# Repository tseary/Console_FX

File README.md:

# Console_FX
Controller for steam power plant control console "light show".

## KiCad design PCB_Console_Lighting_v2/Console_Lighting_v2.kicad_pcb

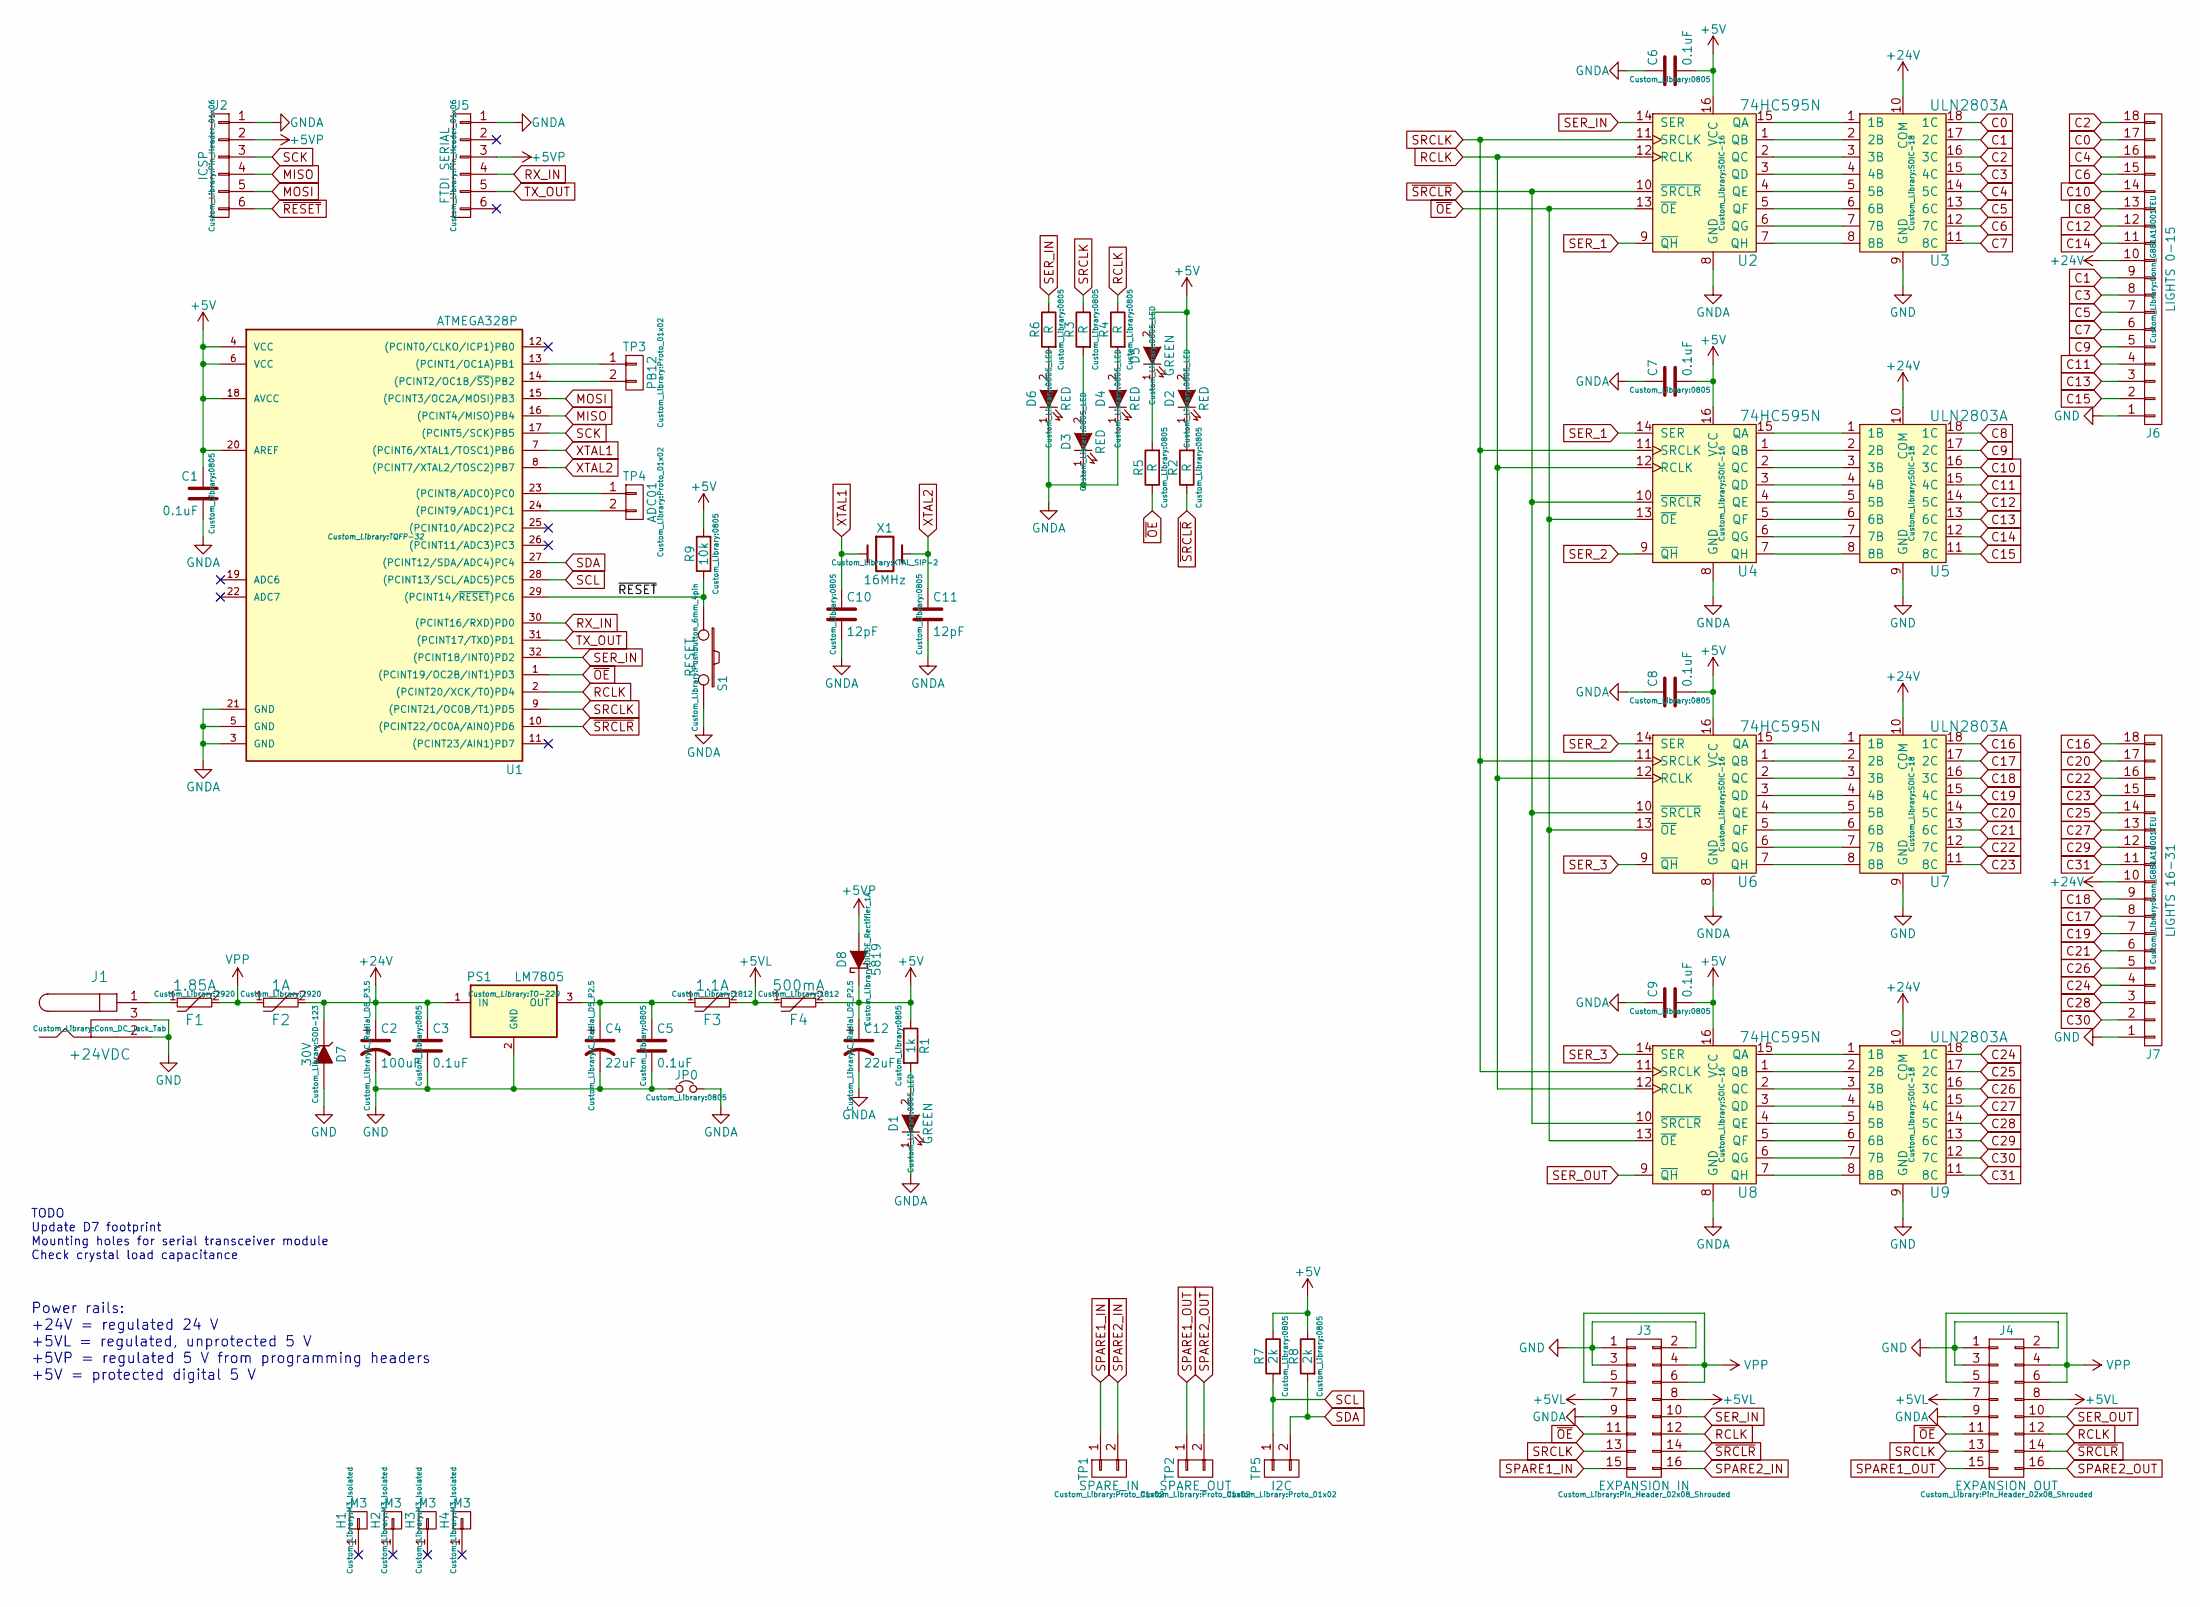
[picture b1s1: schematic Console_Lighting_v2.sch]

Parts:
C1, C3, C5, C6, C7, C8, C9: 0.1uF; 0805
C2: 100uF; C_Radial_D8_P3.5
C4, C12: 22uF; C_Radial_D5_P2.5
C10, C11: 12pF; 0805
D1, D5: GREEN; 0805_LED
D2, D3, D4, D6: RED; 0805_LED
D7: 30V; SOD-123
D8: 5819; DIODE_Rectifier_1A
F1: 1.85A; 2920
F2: 1A; 2920
F3: 1.1A; 1812
F4: 500mA; 1812
H1, H2, H3, H4: M3; M3_Isolated
J1: +24VDC; Conn_DC_Jack_Tab
J2: ICSP; Pin_Header_01x06
J3: EXPANSION IN; Pin_Header_02x08_Shrouded
J4: EXPANSION OUT; Pin_Header_02x08_Shrouded
J5: FTDI SERIAL; Pin_Header_01x06
J6: LIGHTS 0-15; Conn_G881A18001TEU
J7: LIGHTS 16-31; Conn_G881A18001TEU
JP0: Jumper_NC_Small; 0805
PS1: LM7805; TO-220
R1: 1k; 0805
R2, R3, R4, R5, R6: R; 0805
R7, R8: 2k; 0805
R9: 10k; 0805
S1: RESET; Pushbutton_6mm_4pin
TP1: SPARE_IN; Proto_01x02
TP2: SPARE_OUT; Proto_01x02
TP3: PB12; Proto_01x02
TP4: ADC01; Proto_01x02
TP5: I2C; Proto_01x02
U1: ATMEGA328P; TQFP-32
U2, U4, U6, U8: 74HC595N; SOIC-16
U3, U5, U7, U9: ULN2803A; SOIC-18
X1: 16MHz; XTAL_SIP-2

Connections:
+5V: C1.1, C6.2, C7.2, C8.2, C9.2, C12.1, D2.2 (A), D5.2 (A), D8.1 (K), F4.2, R1.1, R7.1, R8.1, R9.2, U1.4 (VCC), U1.6 (VCC), U1.18 (AVCC), U1.20 (AREF), U2.16 (VCC), U4.16 (VCC), U6.16 (VCC), U8.16 (VCC)
+5VL: F3.2, F4.1, J3.7, J3.8, J4.7, J4.8
+5VP: D8.2 (A), J2.2, J5.3
+24V: C2.1, C3.1, D7.1 (K), F2.2, J6.10, J7.10, PS1.1 (IN), U3.10 (COM), U5.10 (COM), U7.10 (COM), U9.10 (COM)
C0: J6.17, U3.18 (1C)
C1: J6.9, U3.17 (2C)
C2: J6.18, U3.16 (3C)
C3: J6.8, U3.15 (4C)
C4: J6.16, U3.14 (5C)
C5: J6.7, U3.13 (6C)
C6: J6.15, U3.12 (7C)
C7: J6.6, U3.11 (8C)
C8: J6.13, U5.18 (1C)
C9: J6.5, U5.17 (2C)
C10: J6.14, U5.16 (3C)
C11: J6.4, U5.15 (4C)
C12: J6.12, U5.14 (5C)
C13: J6.3, U5.13 (6C)
C14: J6.11, U5.12 (7C)
C15: J6.2, U5.11 (8C)
C16: J7.18, U7.18 (1C)
C17: J7.8, U7.17 (2C)
C18: J7.9, U7.16 (3C)
C19: J7.7, U7.15 (4C)
C20: J7.17, U7.14 (5C)
C21: J7.6, U7.13 (6C)
C22: J7.16, U7.12 (7C)
C23: J7.15, U7.11 (8C)
C24: J7.4, U9.18 (1C)
C25: J7.14, U9.17 (2C)
C26: J7.5, U9.16 (3C)
C27: J7.13, U9.15 (4C)
C28: J7.3, U9.14 (5C)
C29: J7.12, U9.13 (6C)
C30: J7.2, U9.12 (7C)
C31: J7.11, U9.11 (8C)
GND: C2.2, C3.2, C4.2, C5.2, D7.2 (A), J1.2, J1.3, J3.1, J3.2, J3.3, J4.1, J4.2, J4.3, J6.1, J7.1, JP0.1, PS1.2 (GND), U3.9 (GND), U5.9 (GND), U7.9 (GND), U9.9 (GND)
GNDA: C1.2, C6.1, C7.1, C8.1, C9.1, C10.2, C11.2, C12.2, D1.1 (K), D3.1 (K), D4.1 (K), D6.1 (K), J2.1, J3.9, J4.9, J5.1, JP0.2, S1.2, U1.3 (GND), U1.5 (GND), U1.21 (GND), U2.8 (GND), U4.8 (GND), U6.8 (GND), U8.8 (GND)
MISO: J2.4, U1.16 ((PCINT4/MISO)PB4)
MOSI: J2.5, U1.15 ((PCINT3/OC2A/MOSI)PB3)
unnamed: C4.1, C5.1, F3.1, PS1.3 (OUT)
unnamed: D1.2 (A), R1.2
unnamed: D2.1 (K), R2.2
unnamed: D3.2 (A), R3.2
unnamed: D4.2 (A), R4.2
unnamed: D5.1 (K), R5.2
unnamed: D6.2 (A), R6.2
unnamed: F1.1, J1.1
unnamed: TP3.1, U1.13 ((PCINT1/OC1A)PB1)
unnamed: TP3.2, U1.14 ((PCINT2/OC1B/~SS~)PB2)
unnamed: TP4.1, U1.23 ((PCINT8/ADC0)PC0)
unnamed: TP4.2, U1.24 ((PCINT9/ADC1)PC1)
unnamed: U2.1 (QB), U3.2 (2B)
unnamed: U2.2 (QC), U3.3 (3B)
unnamed: U2.3 (QD), U3.4 (4B)
unnamed: U2.4 (QE), U3.5 (5B)
unnamed: U2.5 (QF), U3.6 (6B)
unnamed: U2.6 (QG), U3.7 (7B)
unnamed: U2.7 (QH), U3.8 (8B)
unnamed: U2.15 (QA), U3.1 (1B)
unnamed: U4.1 (QB), U5.2 (2B)
unnamed: U4.2 (QC), U5.3 (3B)
unnamed: U4.3 (QD), U5.4 (4B)
unnamed: U4.4 (QE), U5.5 (5B)
unnamed: U4.5 (QF), U5.6 (6B)
unnamed: U4.6 (QG), U5.7 (7B)
unnamed: U4.7 (QH), U5.8 (8B)
unnamed: U4.15 (QA), U5.1 (1B)
unnamed: U6.1 (QB), U7.2 (2B)
unnamed: U6.2 (QC), U7.3 (3B)
unnamed: U6.3 (QD), U7.4 (4B)
unnamed: U6.4 (QE), U7.5 (5B)
unnamed: U6.5 (QF), U7.6 (6B)
unnamed: U6.6 (QG), U7.7 (7B)
unnamed: U6.7 (QH), U7.8 (8B)
unnamed: U6.15 (QA), U7.1 (1B)
unnamed: U8.1 (QB), U9.2 (2B)
unnamed: U8.2 (QC), U9.3 (3B)
unnamed: U8.3 (QD), U9.4 (4B)
unnamed: U8.4 (QE), U9.5 (5B)
unnamed: U8.5 (QF), U9.6 (6B)
unnamed: U8.6 (QG), U9.7 (7B)
unnamed: U8.7 (QH), U9.8 (8B)
unnamed: U8.15 (QA), U9.1 (1B)
RCLK: J3.12, J4.12, R4.1, U1.2 ((PCINT20/XCK/T0)PD4), U2.12 (RCLK), U4.12 (RCLK), U6.12 (RCLK), U8.12 (RCLK)
RX_IN: J5.4, U1.30 ((PCINT16/RXD)PD0)
SCK: J2.3, U1.17 ((PCINT5/SCK)PB5)
SCL: R7.2, TP5.1, U1.28 ((PCINT13/SCL/ADC5)PC5)
SDA: R8.2, TP5.2, U1.27 ((PCINT12/SDA/ADC4)PC4)
SER_1: U2.9 (~QH), U4.14 (SER)
SER_2: U4.9 (~QH), U6.14 (SER)
SER_3: U6.9 (~QH), U8.14 (SER)
SER_IN: J3.10, R6.1, U1.32 ((PCINT18/INT0)PD2), U2.14 (SER)
SER_OUT: J4.10, U8.9 (~QH)
SPARE1_IN: J3.15, TP1.1
SPARE1_OUT: J4.15, TP2.1
SPARE2_IN: J3.16, TP1.2
SPARE2_OUT: J4.16, TP2.2
SRCLK: J3.13, J4.13, R3.1, U1.9 ((PCINT21/OC0B/T1)PD5), U2.11 (SRCLK), U4.11 (SRCLK), U6.11 (SRCLK), U8.11 (SRCLK)
TX_OUT: J5.5, U1.31 ((PCINT17/TXD)PD1)
VPP: F1.2, F2.1, J3.4, J3.5, J3.6, J4.4, J4.5, J4.6
XTAL1: C10.1, U1.7 ((PCINT6/XTAL1/TOSC1)PB6), X1.1
XTAL2: C11.1, U1.8 ((PCINT7/XTAL2/TOSC2)PB7), X1.2
~OE: J3.11, J4.11, R5.1, U1.1 ((PCINT19/OC2B/INT1)PD3), U2.13 (~OE), U4.13 (~OE), U6.13 (~OE), U8.13 (~OE)
~RESET: J2.6, R9.1, S1.1, U1.29 ((PCINT14/~RESET~)PC6)
~SRCLR: J3.14, J4.14, R2.1, U1.10 ((PCINT22/OC0A/AIN0)PD6), U2.10 (~SRCLR), U4.10 (~SRCLR), U6.10 (~SRCLR), U8.10 (~SRCLR)

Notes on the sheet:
TODO Update D7 footprint Mounting holes for serial transceiver module Check crystal load capacitance
Power rails: +24V = regulated 24 V +5VL = regulated, unprotected 5 V +5VP = regulated 5 V from programming headers +5V = protected digital 5 V

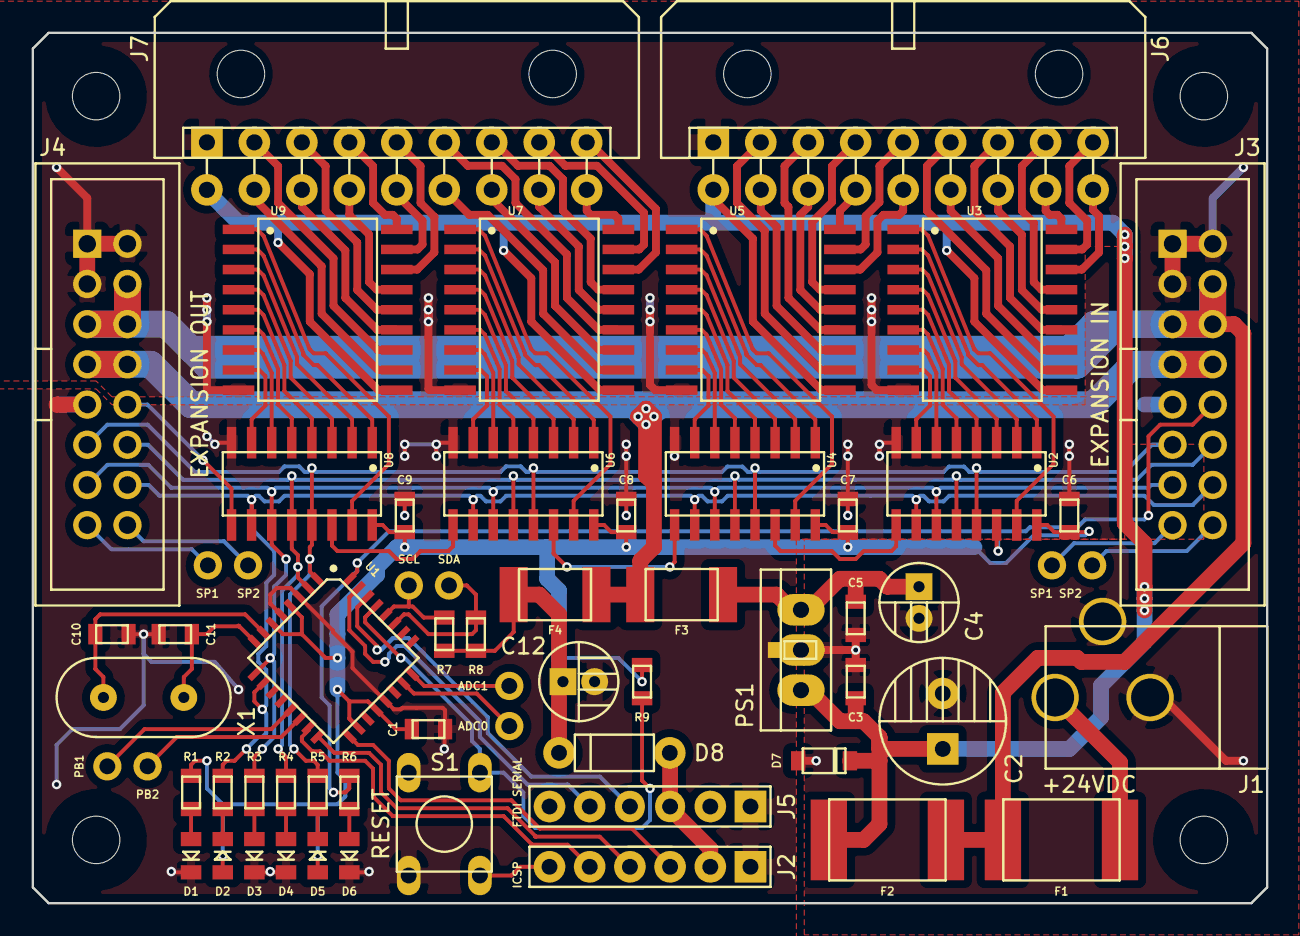
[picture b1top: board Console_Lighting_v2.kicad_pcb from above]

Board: 2 copper layers, 78.0 x 55.0 mm, 62 parts (0 on the bottom side), 106 nets.

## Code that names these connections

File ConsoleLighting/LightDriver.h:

#pragma once

#include <Arduino.h>
#include <stdint.h>

enum LightMode : uint8_t {
	LIGHT_MODE_OFF,
	LIGHT_MODE_ON,
	LIGHT_MODE_FLASH_FAST,
	LIGHT_MODE_FLASH_SLOW,
	LIGHT_MODE_FLASH_FLASH_DOUBLE_FLASH,
	LightMode_Length	// The number of valid members of the enum
};

class LightDriver {
public:
	LightDriver(uint8_t lightCount) {
		// Set up light fields
		_lightCount = lightCount;
		_lightModes = new LightMode[lightCount];
		_lightOutputsLength = (lightCount + 7) / 8;
		_lightOutputs = new uint8_t[_lightOutputsLength];

		// Set up pins
		pinMode(_outputEnablePin, OUTPUT);
		pinMode(_shiftRegClearPin, OUTPUT);
		pinMode(_shiftRegDataPin, OUTPUT);
		pinMode(_shiftRegClockPin, OUTPUT);
		pinMode(_outputRegClockPin, OUTPUT);

		digitalWrite(_shiftRegDataPin, LOW);	// Data 0
		digitalWrite(_shiftRegClockPin, LOW);	// Shift clock inactive
		digitalWrite(_outputRegClockPin, LOW);	// Output clock inactive

		// Clear the registers
		reset();
		setAllLightModes(LIGHT_MODE_OFF);
	}
	~LightDriver() {
		delete[] _lightOutputs;
	}

	// Clears the shift and output registers and enables the outputs.
	// Does not change light modes that have been set.
	void reset();

	uint8_t getLightCount() {
		return _lightCount;
	}

	// Sets the mode of a single light.
	void setLightMode(uint8_t index, LightMode mode);

	// Sets the mode of all lights.
	void setAllLightModes(LightMode mode);

	// Updates all light outputs. Call repeatedly to drive animations.
	void updateOutputs();

	// Gets a human-readable string representing the given light mode.
	static const char* lightModeToString(LightMode lightMode);

protected:
	// Pins
	const uint8_t
		_outputEnablePin = 3,	// PD3, Active low
		_shiftRegClearPin = 6,	// PD6, L = shift register cleared
		_shiftRegDataPin = 2,	// PD2, Data input to shift register
		_shiftRegClockPin = 5,	// PD5, Rising edge = Value at data pin loaded into shift register
		_outputRegClockPin = 4;	// PD4, Rising edge = Data in shift register moves to output

	// Blink timing in millis
	uint16_t
		_flashFastPeriod = 333,
		_flashSlowPeriod = 1000;

	// Lighting control fields
	uint8_t _lightCount;		// The number of outputs connected
	LightMode *_lightModes;	// The function each light is performing
	uint8_t _lightOutputsLength;
	uint8_t *_lightOutputs;		// One bit for each light, representing whether the light is currently on or off

	// Low-level functions
	void clearShiftRegister() {
		digitalWrite(_shiftRegClearPin, LOW);
		delay(1);
		digitalWrite(_shiftRegClearPin, HIGH);
		digitalWrite(_shiftRegDataPin, LOW);
	}

	void loadOutputRegister() {
		digitalWrite(_outputRegClockPin, HIGH);
		delay(1);
		digitalWrite(_outputRegClockPin, LOW);
	}
};

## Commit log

2017-08-30 Initial Commit
    WIP
2017-08-30 Implemented serial command infrastructure
2017-08-30 Added KiCad PCB
    Console Lighting v2 PCB
2017-08-30 Implemented shift register control
    Brought in old code from test sketch to drive shift registers.
2017-08-31 v1.0 Created basic serial commands
